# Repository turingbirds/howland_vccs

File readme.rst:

Practical Measurement of Voltage-Controlled Current Source Output Impedance for Applications in Transcranial Electrical Stimulation
===================================================================================================================================

Welcome to the repository accompanying the conference paper:

    \C\. Linssen and P. Harpe, "Practical Measurement of Voltage-Controlled Current Source Output Impedance for Applications in Transcranial Electrical Stimulation," 2021 IEEE Biomedical Circuits and Systems Conference (BioCAS), 6–9 Oct 2021, pp. 1–6, doi: `10.1109/BioCAS49922.2021.9644974 <https://doi.org/10.1109/BioCAS49922.2021.9644974>`_.

For BibTeX and other citation formats, please visit https://ieeexplore.ieee.org/document/9644974.

This repository contains the simulations, analysis and plotting scripts, prototype PCB designs and empirical measurement data for reproducing the figures in the paper.

The final paper can be downloaded from https://ieeexplore.ieee.org/document/9644974. The IEEE policy permits (`IEEE Publication Services and Products Board Operations Manual 2021, Section 8.1.9 <https://pspb.ieee.org/images/files/files/opsmanual.pdf>`_) authors to disseminate 'preprint' versions of their papers. This 'author preprint version' can be found under `paper/ <paper>`_ and corresponds to the peer-reviewed manuscript submitted as the final version to the conference.

The unabridged preprint, which was *not peer reviewed*, contains additional background information such a loop stability simulations, that could be helpful in reproducing and iterating upon the results in the paper. This unabridged version can be found under the directory `preprint/ <preprint>`_.

We (the authors of the paper) welcome feedback; please write to the corresponding author at c.linssen@donders.ru.nl.

License
-------

Copyright on the paper (figures, text) is held by IEEE (2021):

*© 2021 IEEE. Personal use of this material is permitted. Permission
from IEEE must be obtained for all other uses, in any current or future
media, including reprinting/republishing this material for advertising or
promotional purposes, creating new collective works, for resale or
redistribution to servers or lists, or reuse of any copyrighted
component of this work in other works.*

All materials on this repository that are not covered by IEEE license or copyright, are Copyright (C) 2021, C. Linssen and P. Harpe, and published here under the Apache License 2.0 license, a copy of which is included in this repository at `apache_license_2.0.txt <apache_license_2.0.txt>`_.

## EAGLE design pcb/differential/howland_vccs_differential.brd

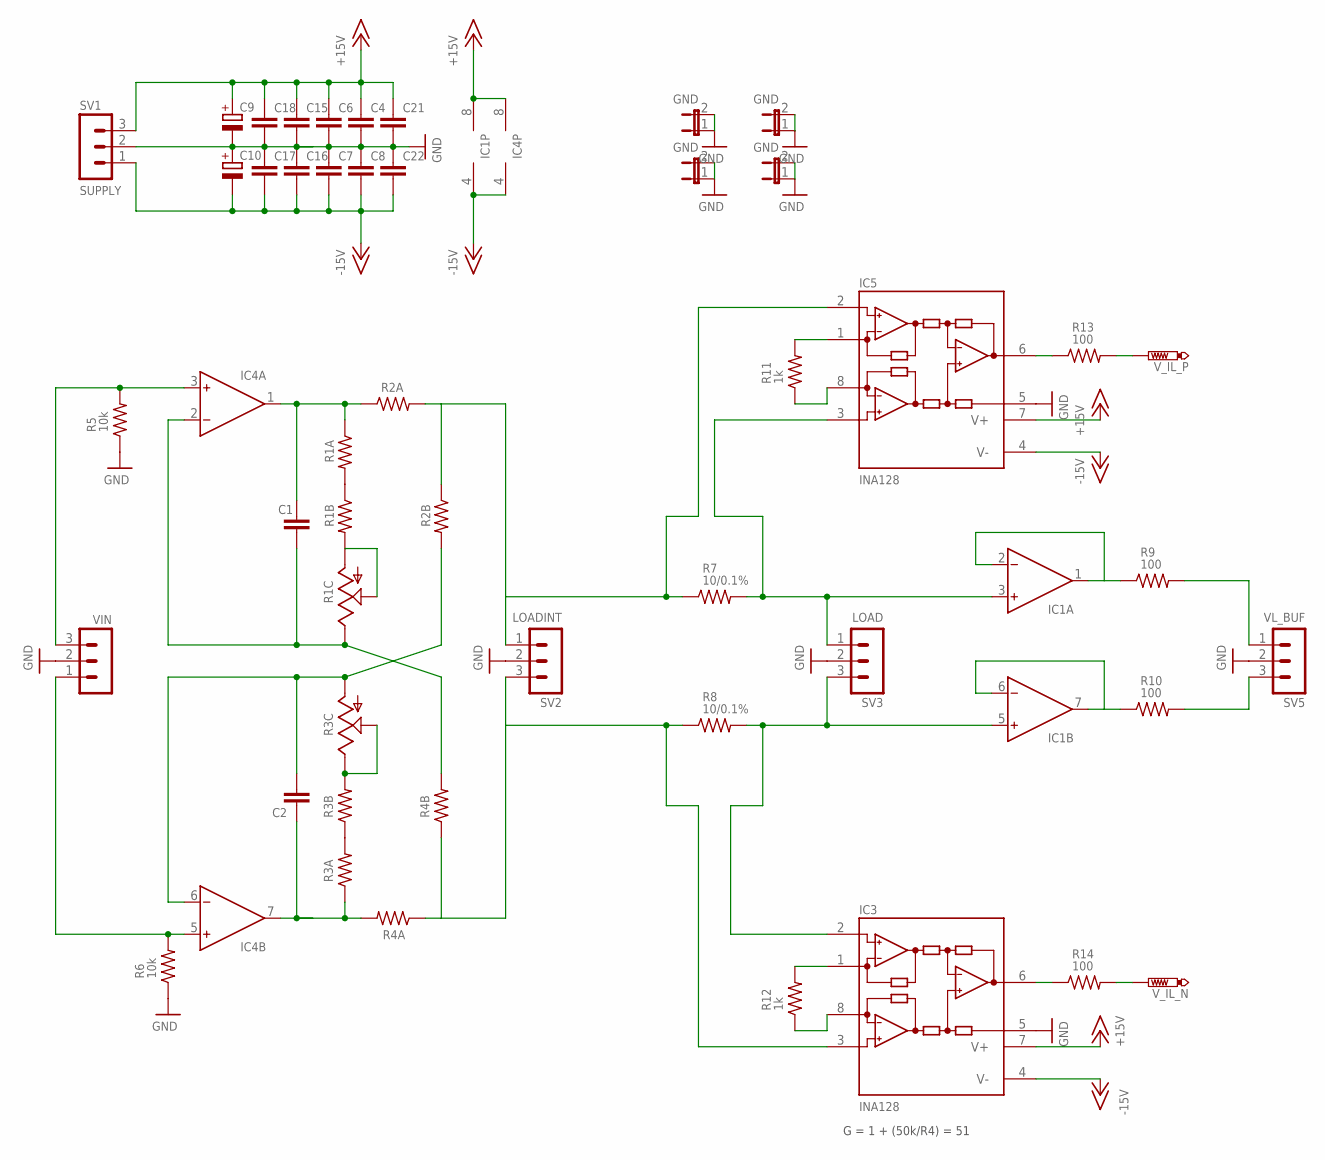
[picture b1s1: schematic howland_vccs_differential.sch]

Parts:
C1, C2, C4, C6, C7, C8, C15, C16, C17, C18, C21, C22: C-EUC1206; C1206
C9, C10: CPOL-EUC/6032-28R; C/6032-28R
IC1, IC4: OPA2192; SO8
IC3, IC5: INA128; SO08
JP8, JP10, JP11, JP12: GND; JP1
R1A, R1B, R2A, R2B, R3A, R3B, R4A, R4B: R-US_R1206; R1206
R1C, R3C: TRIM_US-3223J; 3223J
R5, R6: 10k; R1206
R7, R8: 10/0.1%; R1206
R9, R10, R13, R14: 100; R1206
R11, R12: 1k; R1206
SV1: SUPPLY; MA03-1
SV2: LOADINT; MA03-1
SV3: LOAD; MA03-1
SV5: VL_BUF; MA03-1
VIN: MA03-1
V_IL_N: PTR1PAD1-13; P1-13
V_IL_P: PTR1PAD1-13; P1-13

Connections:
+15V: C4.1, C6.1, C9.+, C15.1, C18.1, C21.1, IC1.8 (V+), IC3.7 (V+), IC4.8 (V+), IC5.7 (V+), SV1.3
-15V: C7.2, C8.2, C10.-, C16.2, C17.2, C22.2, IC1.4 (V-), IC3.4 (V-), IC4.4 (V-), IC5.4 (V-), SV1.1
GND: C4.2, C6.2, C7.1, C8.1, C9.-, C10.+, C15.2, C16.1, C17.1, C18.2, C21.2, C22.1, IC3.5 (REF), IC5.5 (REF), JP8.1, JP8.2, JP10.1, JP10.2, JP11.1, JP11.2, JP12.1, JP12.2, R5.1, R6.1, SV1.2, SV2.2, SV3.2, SV5.2, VIN.2
unnamed: IC5.2 (-IN), R2A.2, R2B.1, R7.1, SV2.1
unnamed: C1.2, IC4.2 (IN-), R1C.3 (E), R4B.2
unnamed: C1.1, IC4.1 (OUT), R1A.1, R2A.1
unnamed: IC1.6 (IN-), IC1.7 (OUT), R10.1
unnamed: R1B.2, R1C.1 (A), R1C.2 (S)
unnamed: IC3.1 (RG), R12.2
unnamed: IC3.8 (RG), R12.1
unnamed: IC3.6 (OUT), R14.1
unnamed: R1A.2, R1B.1
unnamed: IC1.1 (OUT), IC1.2 (IN-), R9.1
unnamed: IC4.5 (IN+), R6.2, VIN.1
unnamed: IC4.3 (IN+), R5.2, VIN.3
unnamed: R10.2, SV5.3
unnamed: R14.2, V_IL_N.TP
unnamed: R9.2, SV5.1
unnamed: C2.2, IC4.6 (IN-), R2B.2, R3C.1 (A)
unnamed: C2.1, IC4.7 (OUT), R3A.1, R4A.2
unnamed: R3B.2, R3C.2 (S), R3C.3 (E)
unnamed: IC5.1 (RG), R11.2
unnamed: IC5.8 (RG), R11.1
unnamed: IC5.6 (OUT), R13.1
unnamed: R13.2, V_IL_P.TP
unnamed: IC1.3 (IN+), IC5.3 (+IN), R7.2, SV3.1
unnamed: R3A.2, R3B.1
unnamed: IC3.3 (+IN), R4A.1, R4B.1, R8.1, SV2.3
unnamed: IC1.5 (IN+), IC3.2 (-IN), R8.2, SV3.3

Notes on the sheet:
G = 1 + (50k/R4) = 51

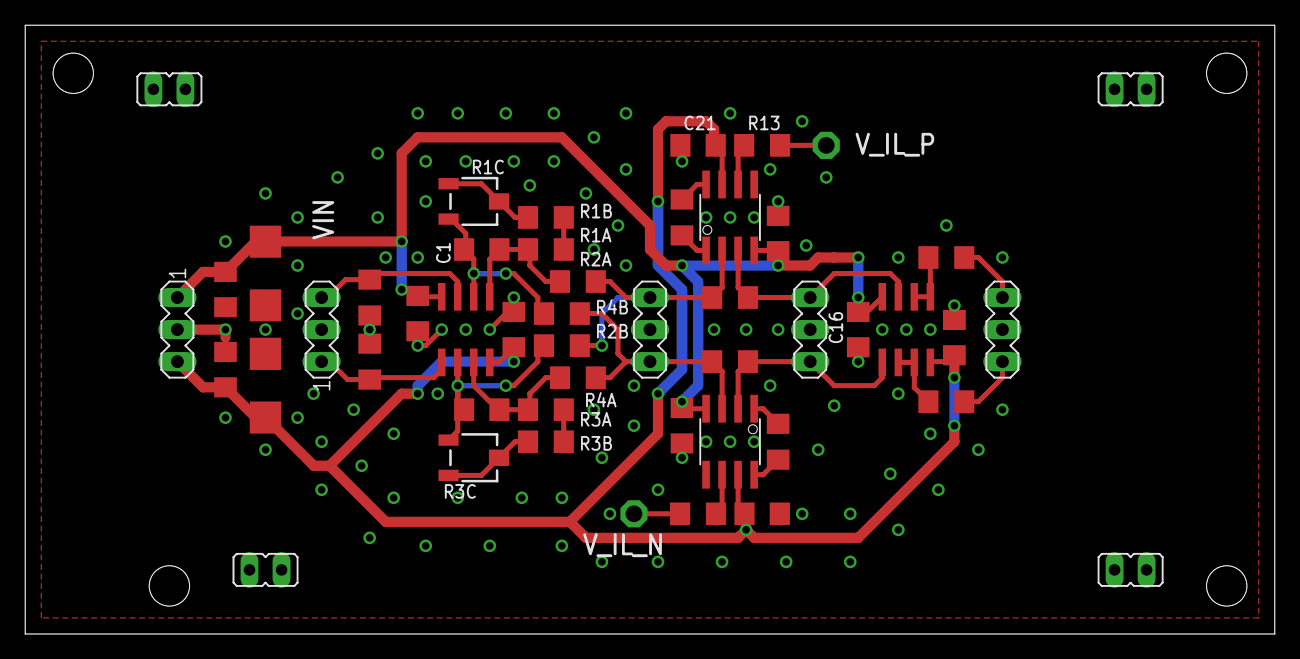
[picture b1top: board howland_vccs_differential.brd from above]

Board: 2 copper layers, 99.1 x 48.3 mm, 49 parts (0 on the bottom side), 29 nets.

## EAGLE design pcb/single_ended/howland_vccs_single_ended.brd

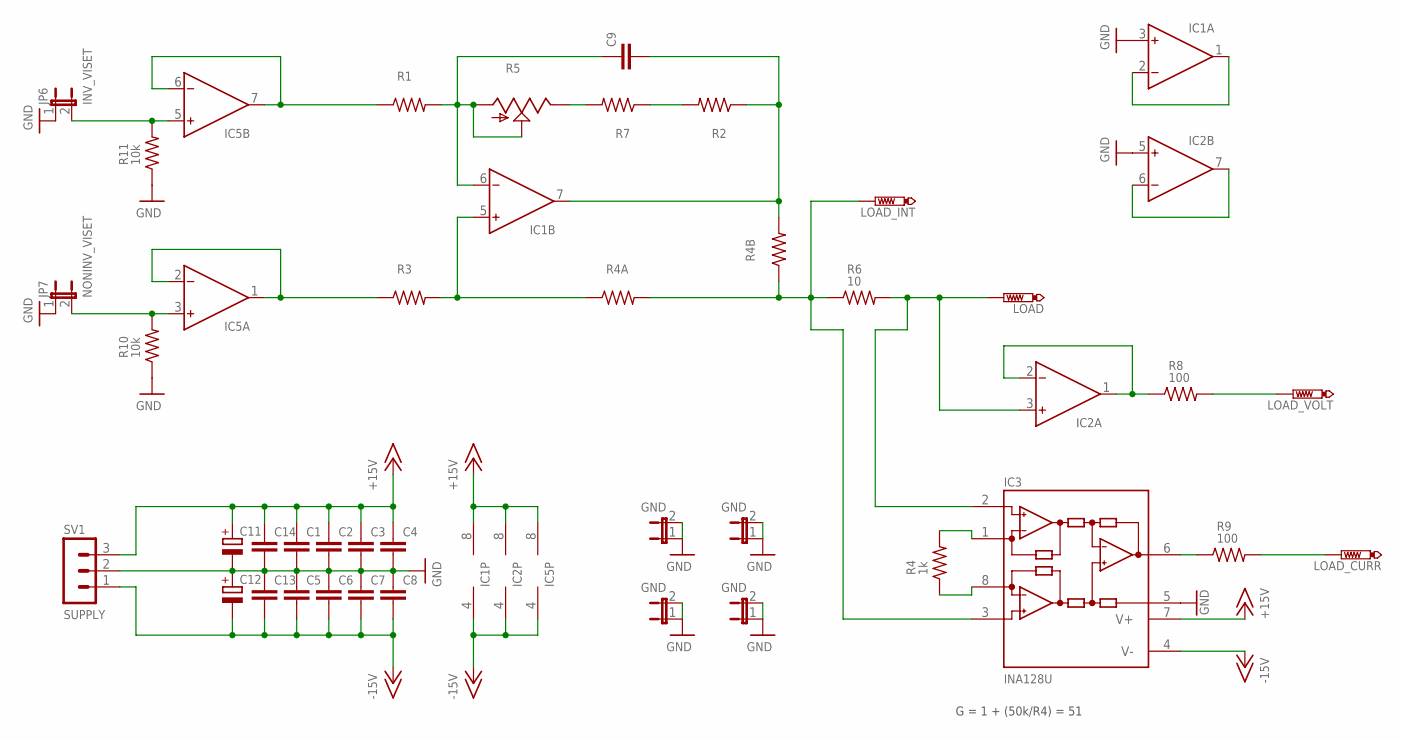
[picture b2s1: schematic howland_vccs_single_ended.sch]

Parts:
C1, C2, C3, C4, C5, C6, C7, C8, C9, C13, C14: C-EUC1206; C1206
C11, C12: CPOL-EUC/6032-28R; C/6032-28R
IC1, IC2: LM358; SO8
IC3: INA128U; SO08
IC5: OPA2192; SO8
JP4, JP8, JP9, JP10: GND; JP1
JP6: INV_VISET; JP1
JP7: NONINV_VISET; JP1
LOAD: PTR1PAD1-13; P1-13
LOAD_CURR: PTR1PAD1-13; P1-13
LOAD_INT: PTR1PAD1-13; P1-13
LOAD_VOLT: PTR1PAD1-13; P1-13
R1, R3: 12.25k/0.1%; R1206
R2, R4A: 10k/.1%; R1206
R4: 1k; R1206
R4B: 250; R1206
R5: 100; 3223J
R6: 10; R1206
R7: 200; R1206
R8, R9: 100; R1206
R10, R11: 10k; R1206
SV1: SUPPLY; MA03-1

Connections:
+15V: C1.1, C2.1, C3.1, C4.1, C11.+, C14.1, IC1.8 (V+), IC2.8 (V+), IC3.7 (V+), IC5.8 (V+), SV1.3
-15V: C5.2, C6.2, C7.2, C8.2, C12.-, C13.2, IC1.4 (V-), IC2.4 (V-), IC3.4 (V-), IC5.4 (V-), SV1.1
GND: C1.2, C2.2, C3.2, C4.2, C5.1, C6.1, C7.1, C8.1, C11.-, C12.+, C13.1, C14.2, IC1.3 (IN+), IC2.5 (IN+), IC3.5 (REF), JP4.1, JP4.2, JP6.1, JP7.1, JP8.1, JP8.2, JP9.1, JP9.2, JP10.1, JP10.2, R10.1, R11.1, SV1.2
unnamed: IC2.1 (OUT), IC2.2 (IN-), R8.1
unnamed: IC1.5 (IN+), R3.2, R4A.1
unnamed: C9.1, IC1.6 (IN-), R1.2, R5.1 (A), R5.2 (S)
unnamed: C9.2, IC1.7 (OUT), R2.1, R4B.2
unnamed: IC3.3 (+IN), LOAD_INT.TP, R4A.2, R4B.1, R6.1
unnamed: R5.3 (E), R7.2
unnamed: IC3.1 (RG), R4.2
unnamed: IC3.8 (RG), R4.1
unnamed: IC3.6 (OUT), R9.1
unnamed: IC1.1 (OUT), IC1.2 (IN-)
unnamed: R2.2, R7.1
unnamed: IC5.1 (OUT), IC5.2 (IN-), R3.1
unnamed: IC5.6 (IN-), IC5.7 (OUT), R1.1
unnamed: IC5.3 (IN+), JP7.2, R10.2
unnamed: IC5.5 (IN+), JP6.2, R11.2
unnamed: LOAD_VOLT.TP, R8.2
unnamed: LOAD_CURR.TP, R9.2
unnamed: IC2.6 (IN-), IC2.7 (OUT)
unnamed: IC2.3 (IN+), IC3.2 (-IN), LOAD.TP, R6.2

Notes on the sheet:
G = 1 + (50k/R4) = 51

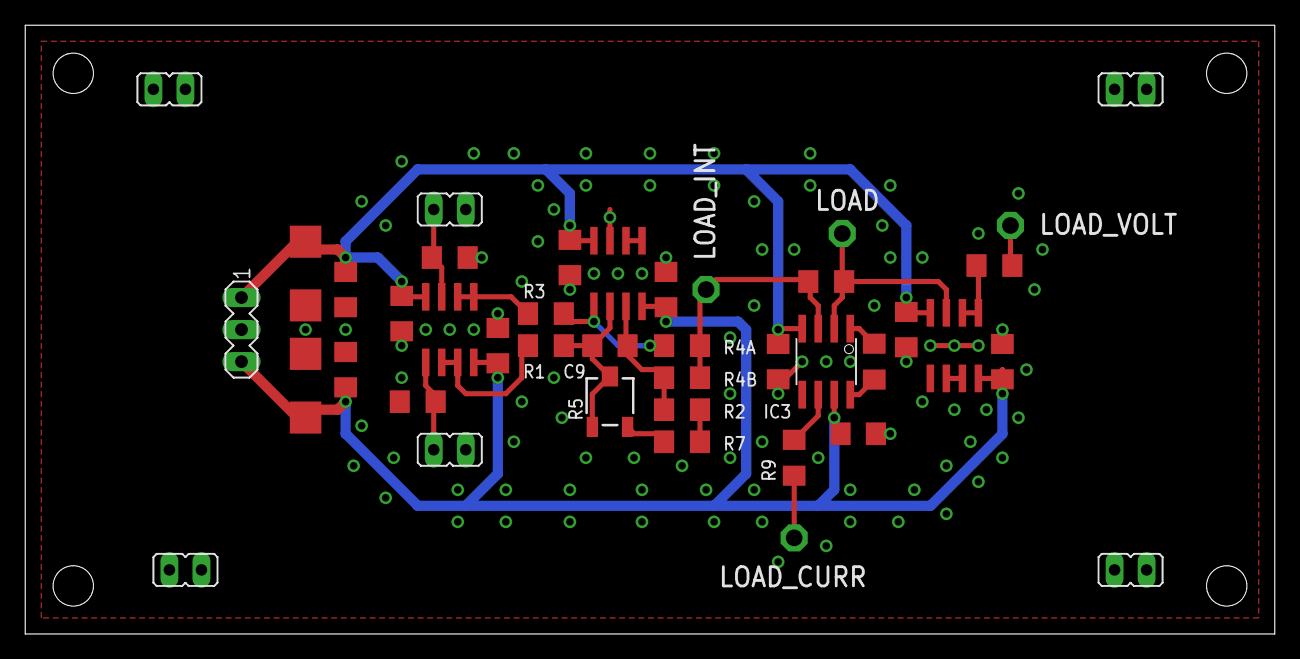
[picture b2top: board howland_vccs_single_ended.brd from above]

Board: 2 copper layers, 99.1 x 48.3 mm, 41 parts (0 on the bottom side), 22 nets.
